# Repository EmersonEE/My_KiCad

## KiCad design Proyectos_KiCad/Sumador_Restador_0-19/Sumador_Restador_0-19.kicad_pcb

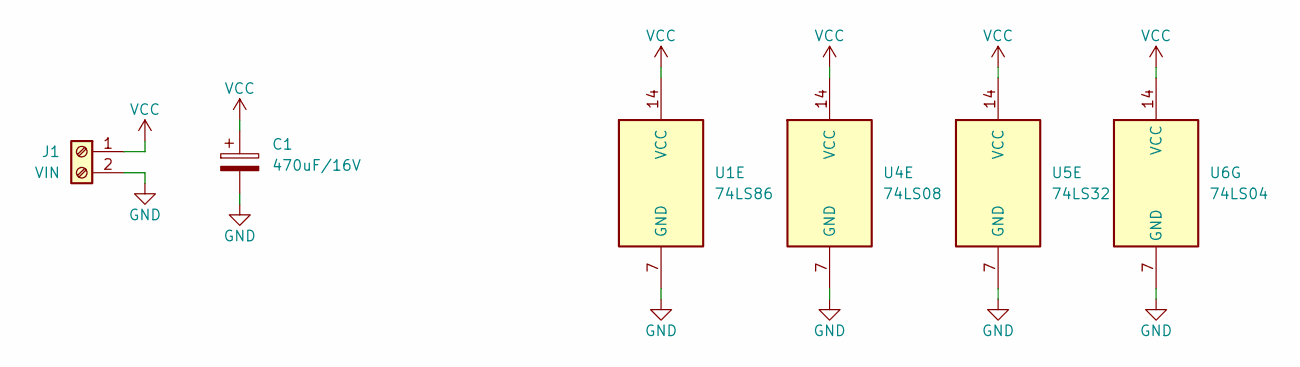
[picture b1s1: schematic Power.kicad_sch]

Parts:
C1: 470uF/16V; CP_Radial_D7.5mm_P2.50mm
J1: VIN; TerminalBlock_Phoenix_MKDS-1,5-2-5.08_1x02_P5.08mm_Horizont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
U1: 74LS86; DIP-14_W7.62mm_LongPads
U4: 74LS08; DIP-14_W7.62mm_LongPads
U5: 74LS32; DIP-14_W7.62mm_LongPads
U6: 74LS04; DIP-14_W7.62mm_LongPads

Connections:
GND: C1.2, J1.2, U1.7 (GND), U4.7 (GND), U5.7 (GND), U6.7 (GND); also elsewhere on the board
VCC: C1.1, J1.1, U1.14 (VCC), U4.14 (VCC), U5.14 (VCC), U6.14 (VCC); also elsewhere on the board

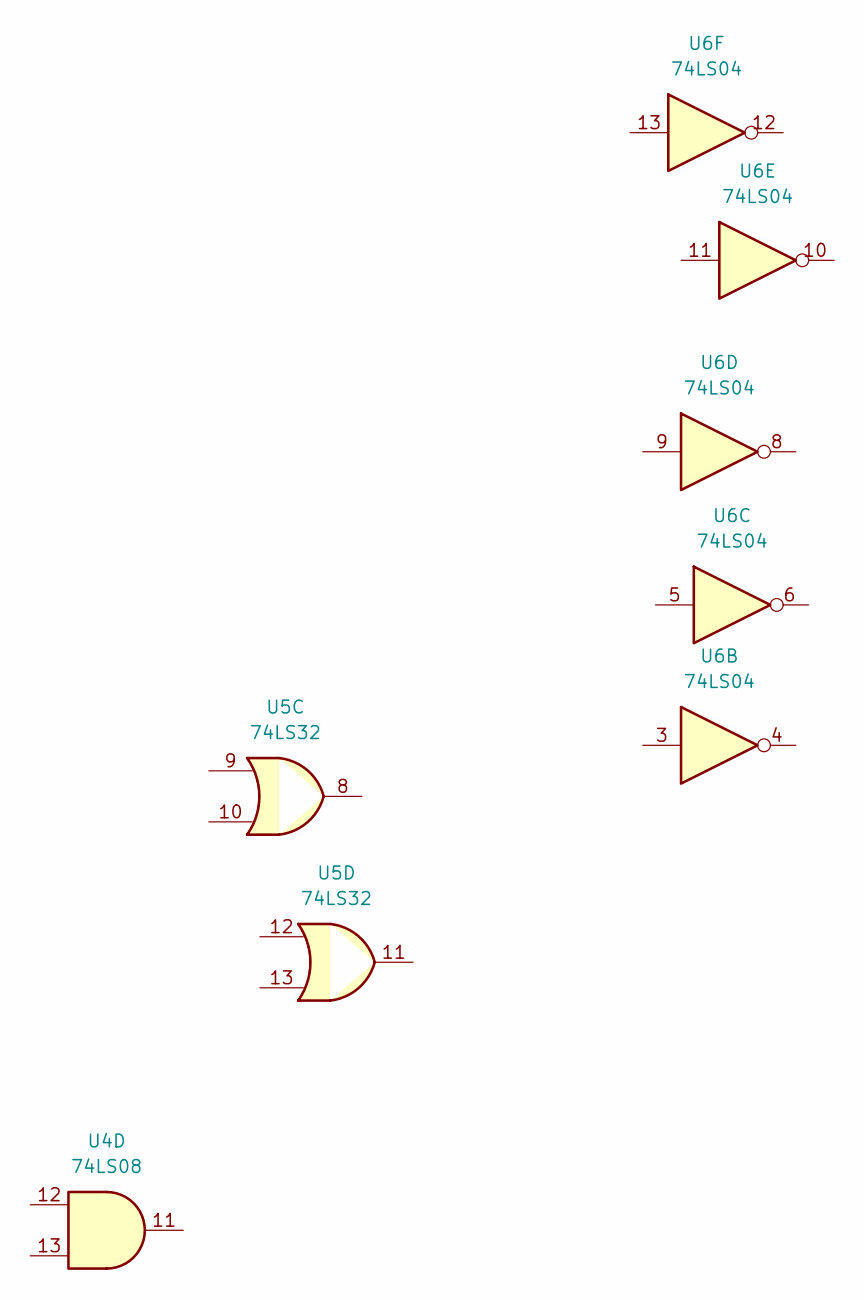
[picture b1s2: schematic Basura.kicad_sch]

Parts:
U4: 74LS08; DIP-14_W7.62mm_LongPads
U5: 74LS32; DIP-14_W7.62mm_LongPads
U6: 74LS04; DIP-14_W7.62mm_LongPads

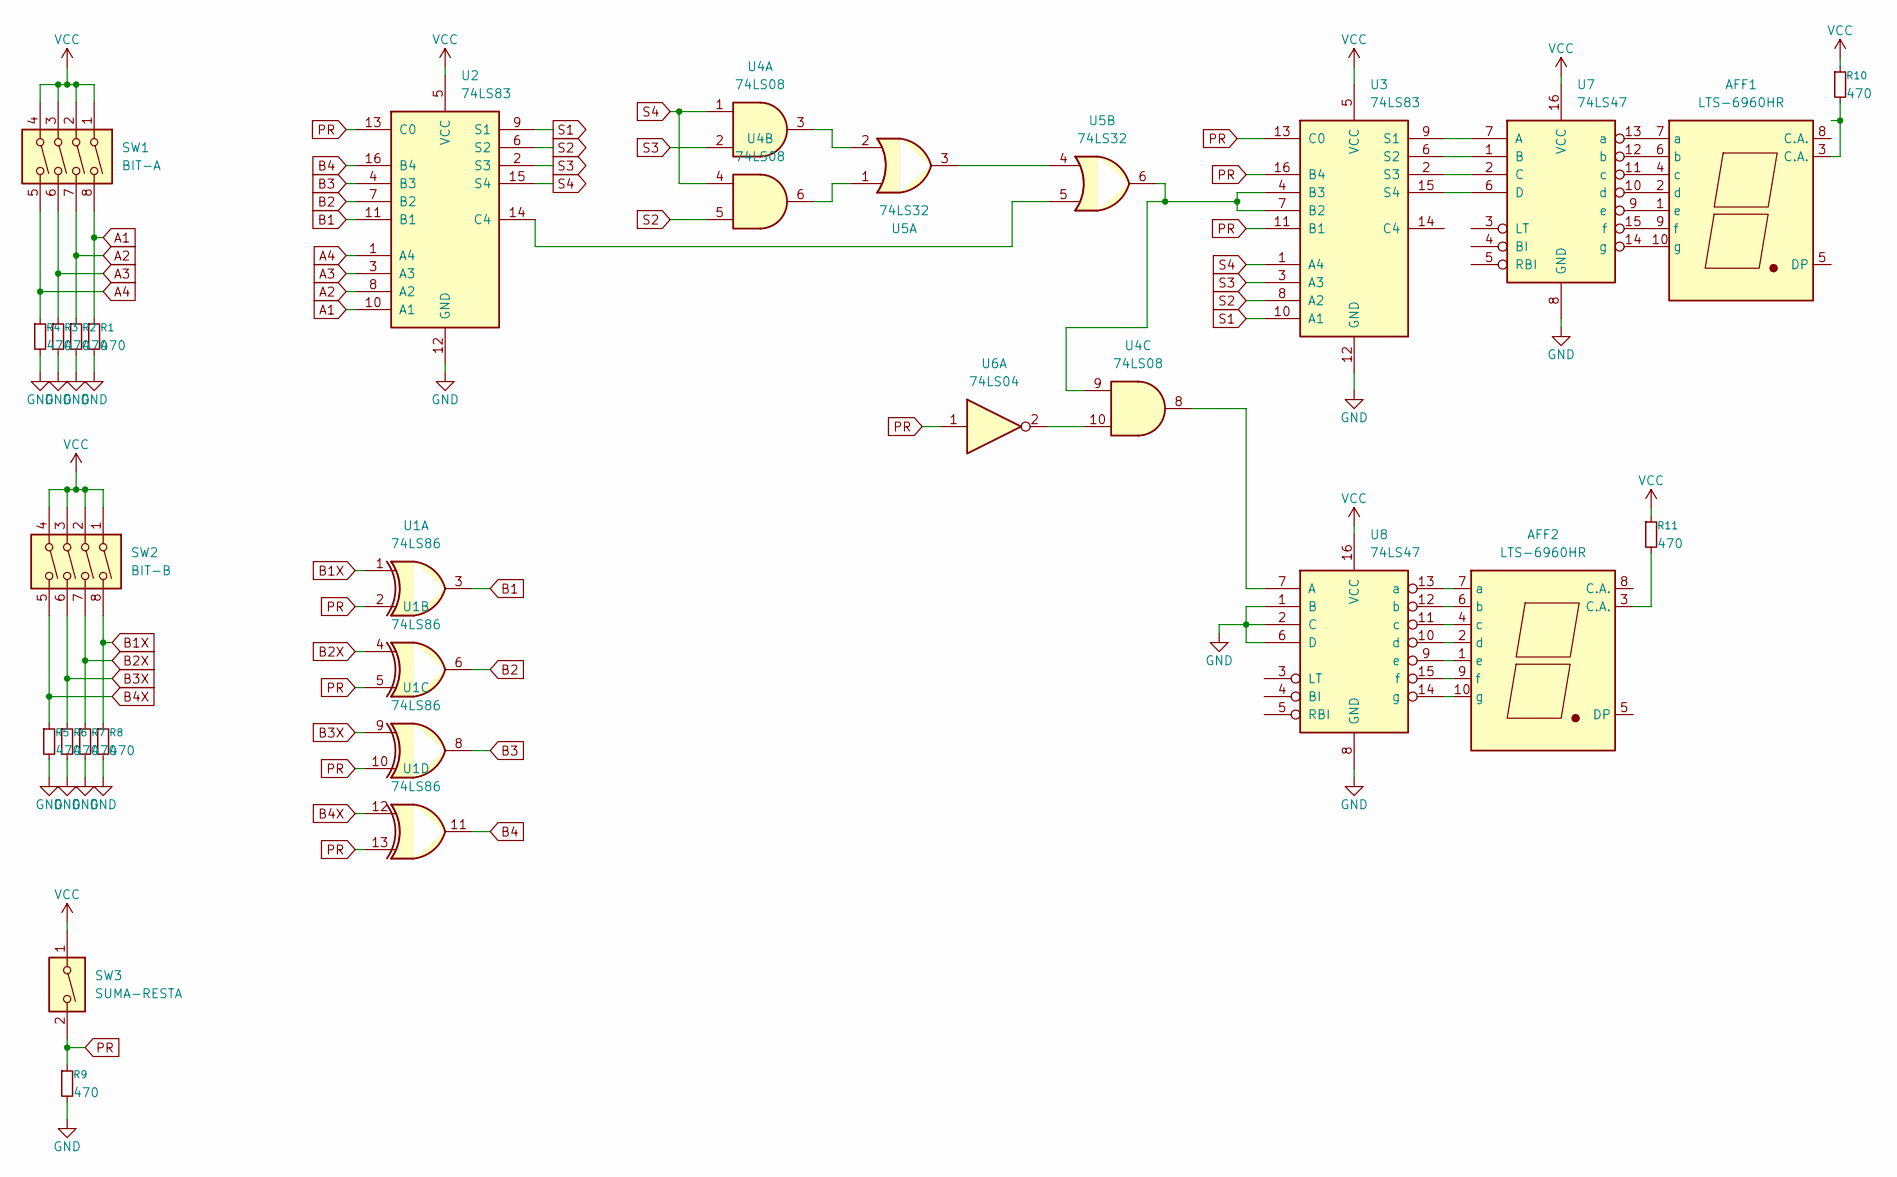
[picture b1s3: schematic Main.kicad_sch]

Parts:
AFF1, AFF2: LTS-6960HR; 7SegmentLED_LTS6760_LTS6780
R1, R2, R3, R4, R5, R6, R7, R8, R9, R10, R11: 470
SW1: BIT-A; SW_DIP_SPSTx04_Slide_9.78x12.34mm_W7.62mm_P2.54mm
SW2: BIT-B; SW_DIP_SPSTx04_Slide_9.78x12.34mm_W7.62mm_P2.54mm
SW3: SUMA-RESTA; SW_DIP_SPSTx01_Slide_9.78x4.72mm_W7.62mm_P2.54mm
U1: 74LS86; DIP-14_W7.62mm_LongPads
U2, U3: 74LS83; DIP-16_W7.62mm_LongPads
U4: 74LS08; DIP-14_W7.62mm_LongPads
U5: 74LS32; DIP-14_W7.62mm_LongPads
U6: 74LS04; DIP-14_W7.62mm_LongPads
U7, U8: 74LS47; DIP-16_W7.62mm_LongPads

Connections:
A1: R1.1, SW1.8, U2.10 (A1)
A2: R2.1, SW1.7, U2.8 (A2)
A3: R3.1, SW1.6, U2.3 (A3)
A4: R4.1, SW1.5, U2.1 (A4)
B1: U1.3, U2.11 (B1)
B1X: R8.1, SW2.8, U1.1
B2: U1.6, U2.7 (B2)
B2X: R7.1, SW2.7, U1.4
B3: U1.8, U2.4 (B3)
B3X: R6.1, SW2.6, U1.9
B4: U1.11, U2.16 (B4)
B4X: R5.1, SW2.5, U1.12
GND: R1.2, R2.2, R3.2, R4.2, R5.2, R6.2, R7.2, R8.2, R9.2, U2.12 (GND), U3.12 (GND), U7.8 (GND), U8.1 (B), U8.2 (C), U8.6 (D), U8.8 (GND); also elsewhere on the board
unnamed: AFF1.3 (C.A.), R10.2
unnamed: AFF1.7 (a), U7.13 (a)
unnamed: AFF1.6 (b), U7.12 (b)
unnamed: AFF1.4 (c), U7.11 (c)
unnamed: AFF1.2 (d), U7.10 (d)
unnamed: AFF1.1 (e), U7.9 (e)
unnamed: AFF1.9 (f), U7.15 (f)
unnamed: AFF1.10 (g), U7.14 (g)
unnamed: AFF2.3 (C.A.), R11.2
unnamed: AFF2.7 (a), U8.13 (a)
unnamed: AFF2.6 (b), U8.12 (b)
unnamed: AFF2.4 (c), U8.11 (c)
unnamed: AFF2.2 (d), U8.10 (d)
unnamed: AFF2.1 (e), U8.9 (e)
unnamed: AFF2.9 (f), U8.15 (f)
unnamed: AFF2.10 (g), U8.14 (g)
unnamed: U2.14 (C4), U5.5
unnamed: U3.4 (B3), U3.7 (B2), U4.9, U5.6
unnamed: U3.9 (S1), U7.7 (A)
unnamed: U3.6 (S2), U7.1 (B)
unnamed: U3.2 (S3), U7.2 (C)
unnamed: U3.15 (S4), U7.6 (D)
unnamed: U4.3, U5.2
unnamed: U4.6, U5.1
unnamed: U4.10, U6.2
unnamed: U5.3, U5.4
unnamed: U4.8, U8.7 (A)
PR: R9.1, SW3.2, U1.2, U1.5, U1.10, U1.13, U2.13 (C0), U3.11 (B1), U3.13 (C0), U3.16 (B4), U6.1
S1: U2.9 (S1), U3.10 (A1)
S2: U2.6 (S2), U3.8 (A2), U4.5
S3: U2.2 (S3), U3.3 (A3), U4.2
S4: U2.15 (S4), U3.1 (A4), U4.1, U4.4
VCC: R10.1, R11.1, SW1.1, SW1.2, SW1.3, SW1.4, SW2.1, SW2.2, SW2.3, SW2.4, SW3.1, U2.5 (VCC), U3.5 (VCC), U7.16 (VCC), U8.16 (VCC); also elsewhere on the board

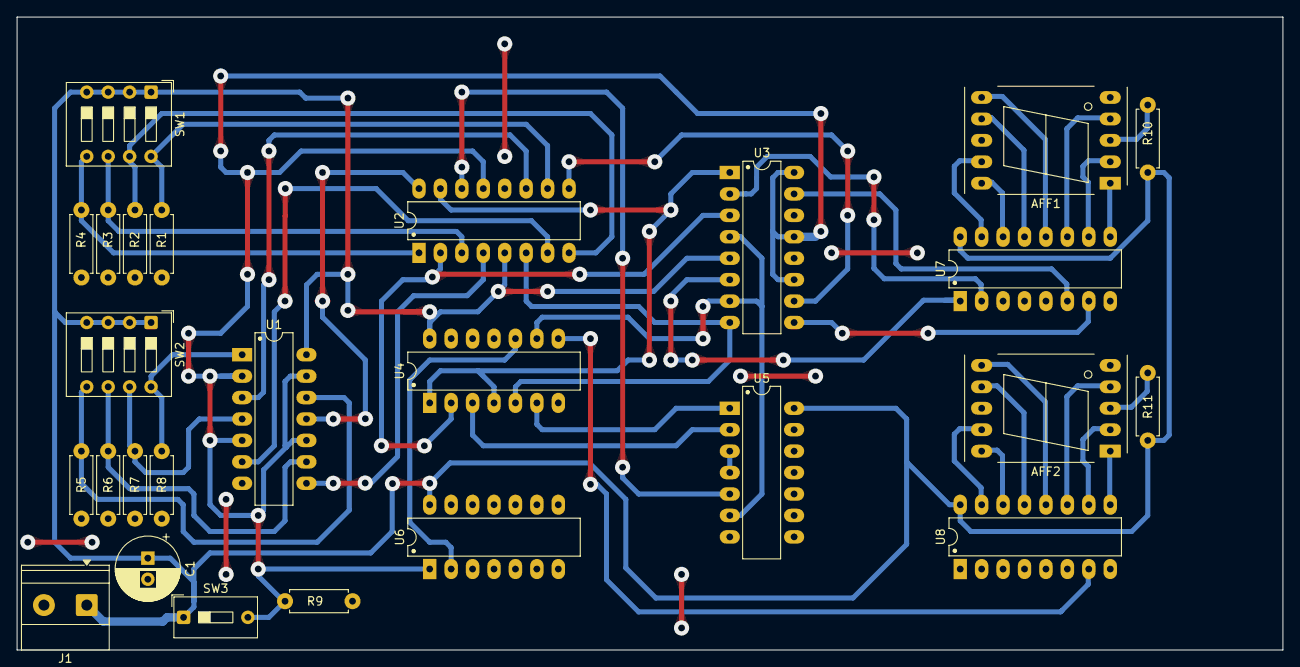
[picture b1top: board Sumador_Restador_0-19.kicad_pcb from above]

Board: 2 copper layers, 150.0 x 75.0 mm, 26 parts (0 on the bottom side), 46 nets.

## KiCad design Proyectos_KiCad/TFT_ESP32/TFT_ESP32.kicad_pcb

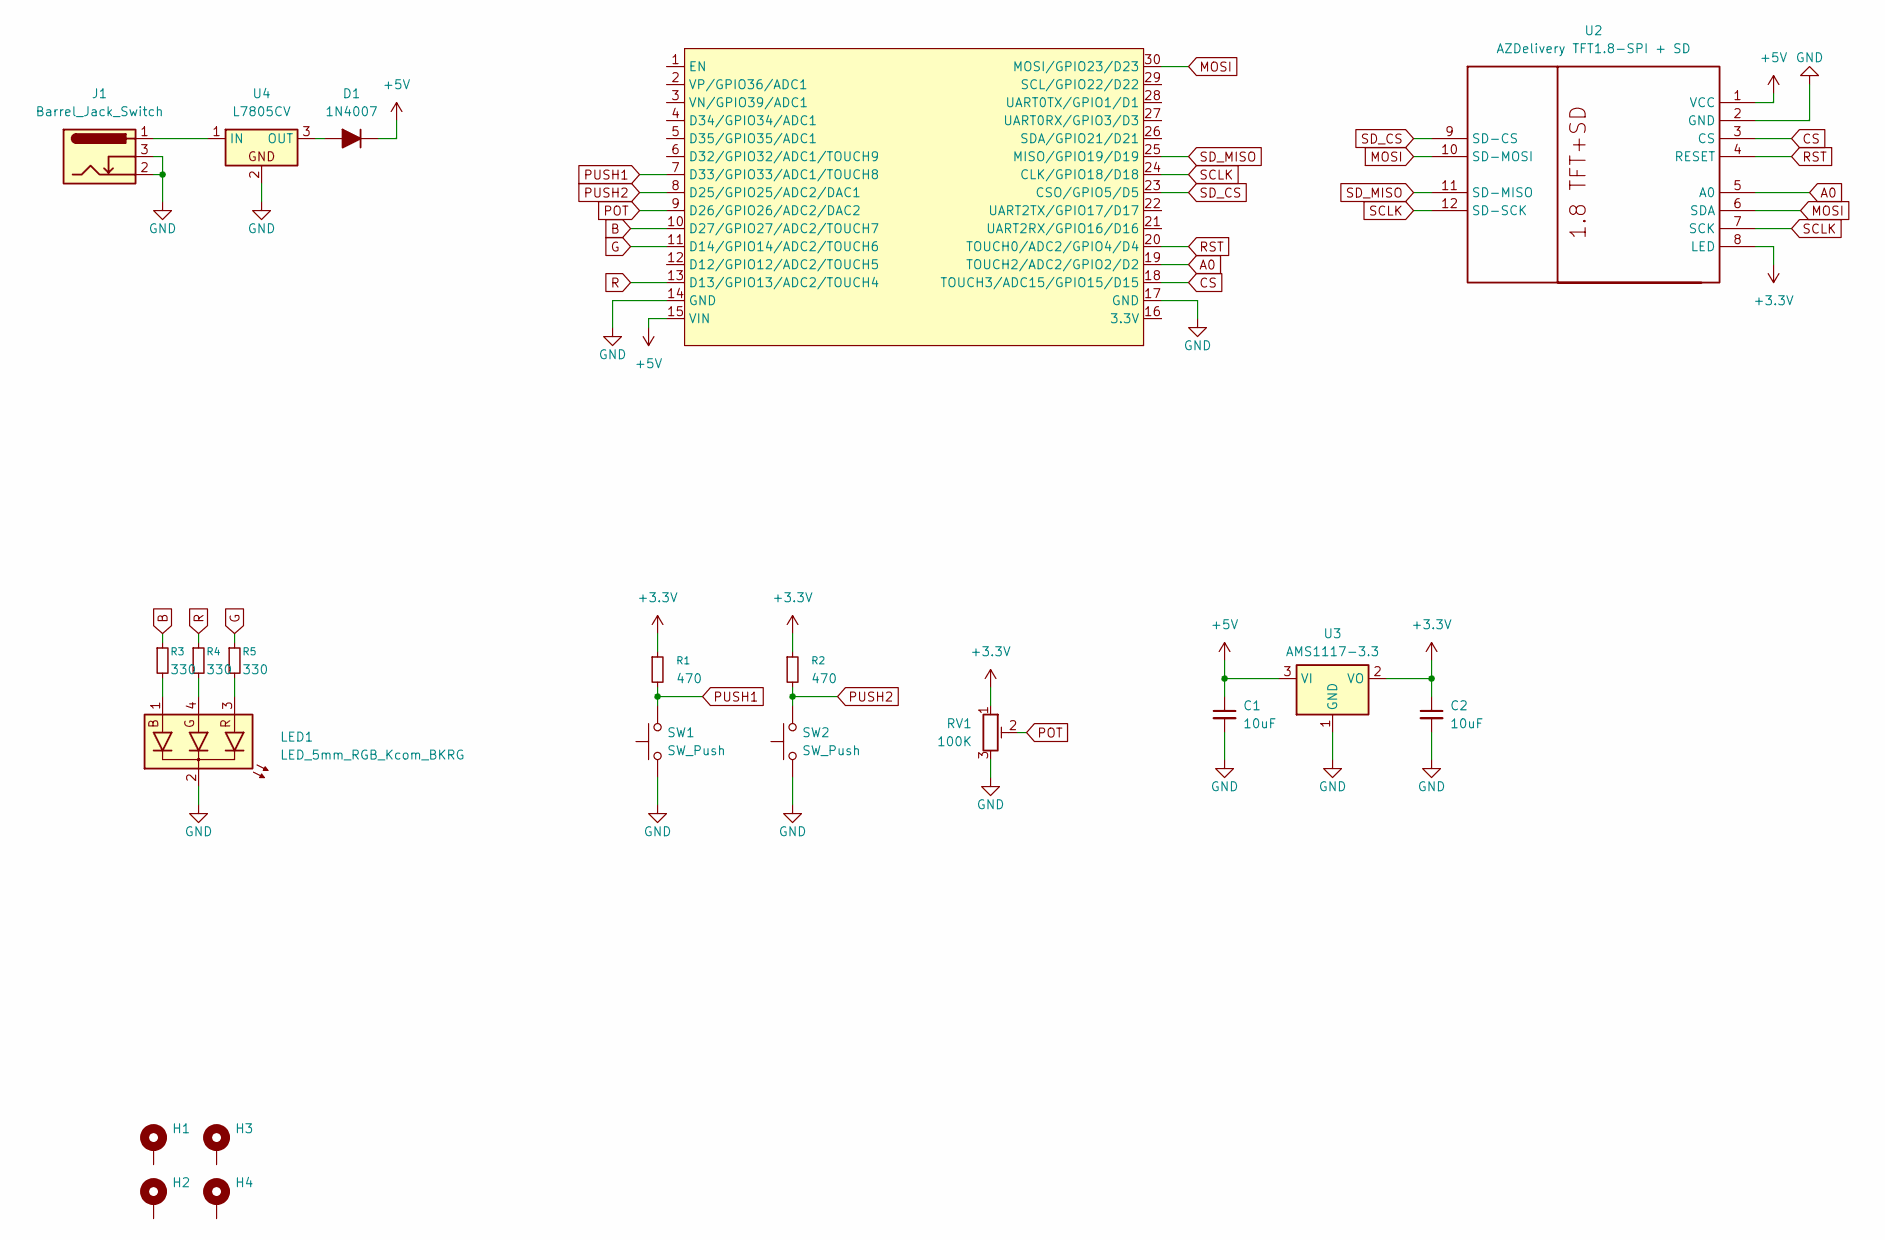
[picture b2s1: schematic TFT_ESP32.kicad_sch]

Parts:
C1, C2: 10uF; C_0805_2012Metric_Pad1.18x1.45mm_HandSolder
D1: 1N4007; D_DO-41_SOD81_P7.62mm_Horizontal
H1, H2, H3, H4: MountingHole_Pad; MountingHole_3.2mm_M3_Pad_Via
J1: Barrel_Jack_Switch; BarrelJack_GCT_DCJ200-10-A_Horizontal
LED1: LED_5mm_RGB_Kcom_BKRG; LED_D5.0mm-4_RGB_Wide_Pins
R1, R2: 470; R_0805_2012Metric_Pad1.20x1.40mm_HandSolder
R3, R4, R5: 330; R_0805_2012Metric_Pad1.20x1.40mm_HandSolder
RV1: 100K; Potentiometer_Bourns_3266Y_Vertical
SW1, SW2: SW_Push; SW_PUSH_6mm
U1: ESP32_DevKit_V1_DOIT; ESP32_DEVKIT_V1_E32
U2: AZDelivery TFT1.8-SPI + SD; 1.8TFT+SD; Manufacturer Part ST7735
U3: AMS1117-3.3; SOT-223-3_TabPin2
U4: L7805CV; TO-220-3_Vertical

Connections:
+3.3V: C2.1, R1.1, R2.1, RV1.1, U2.8 (LED), U3.2 (VO)
+5V: C1.1, D1.1 (K), U1.15 (VIN), U2.1 (VCC), U3.3 (VI)
A0: U1.19 (TOUCH2/ADC2/GPIO2/D2), U2.5 (A0)
B: R3.1, U1.10 (D27/GPIO27/ADC2/TOUCH7)
CS: U1.18 (TOUCH3/ADC15/GPIO15/D15), U2.3 (CS)
G: R5.1, U1.11 (D14/GPIO14/ADC2/TOUCH6)
GND: C1.2, C2.2, J1.2, J1.3, LED1.2 (A), RV1.3, SW1.1, SW2.1, U1.14 (GND), U1.17 (GND), U2.2 (GND), U3.1 (GND), U4.2
MOSI: U1.30 (MOSI/GPIO23/D23), U2.6 (SDA), U2.10 (SD-MOSI)
unnamed: D1.2 (A), U4.3 (OUT)
unnamed: LED1.1 (B), R3.2
unnamed: LED1.4 (G), R4.2
unnamed: LED1.3 (R), R5.2
unnamed: J1.1, U4.1 (IN)
POT: RV1.2, U1.9 (D26/GPIO26/ADC2/DAC2)
PUSH1: R1.2, SW1.2, U1.7 (D33/GPIO33/ADC1/TOUCH8)
PUSH2: R2.2, SW2.2, U1.8 (D25/GPIO25/ADC2/DAC1)
R: R4.1, U1.13 (D13/GPIO13/ADC2/TOUCH4)
RST: U1.20 (TOUCH0/ADC2/GPIO4/D4), U2.4 (RESET)
SCLK: U1.24 (CLK/GPIO18/D18), U2.7 (SCK), U2.12 (SD-SCK)
SD_CS: U1.23 (CSO/GPIO5/D5), U2.9 (SD-CS)
SD_MISO: U1.25 (MISO/GPIO19/D19), U2.11 (SD-MISO)

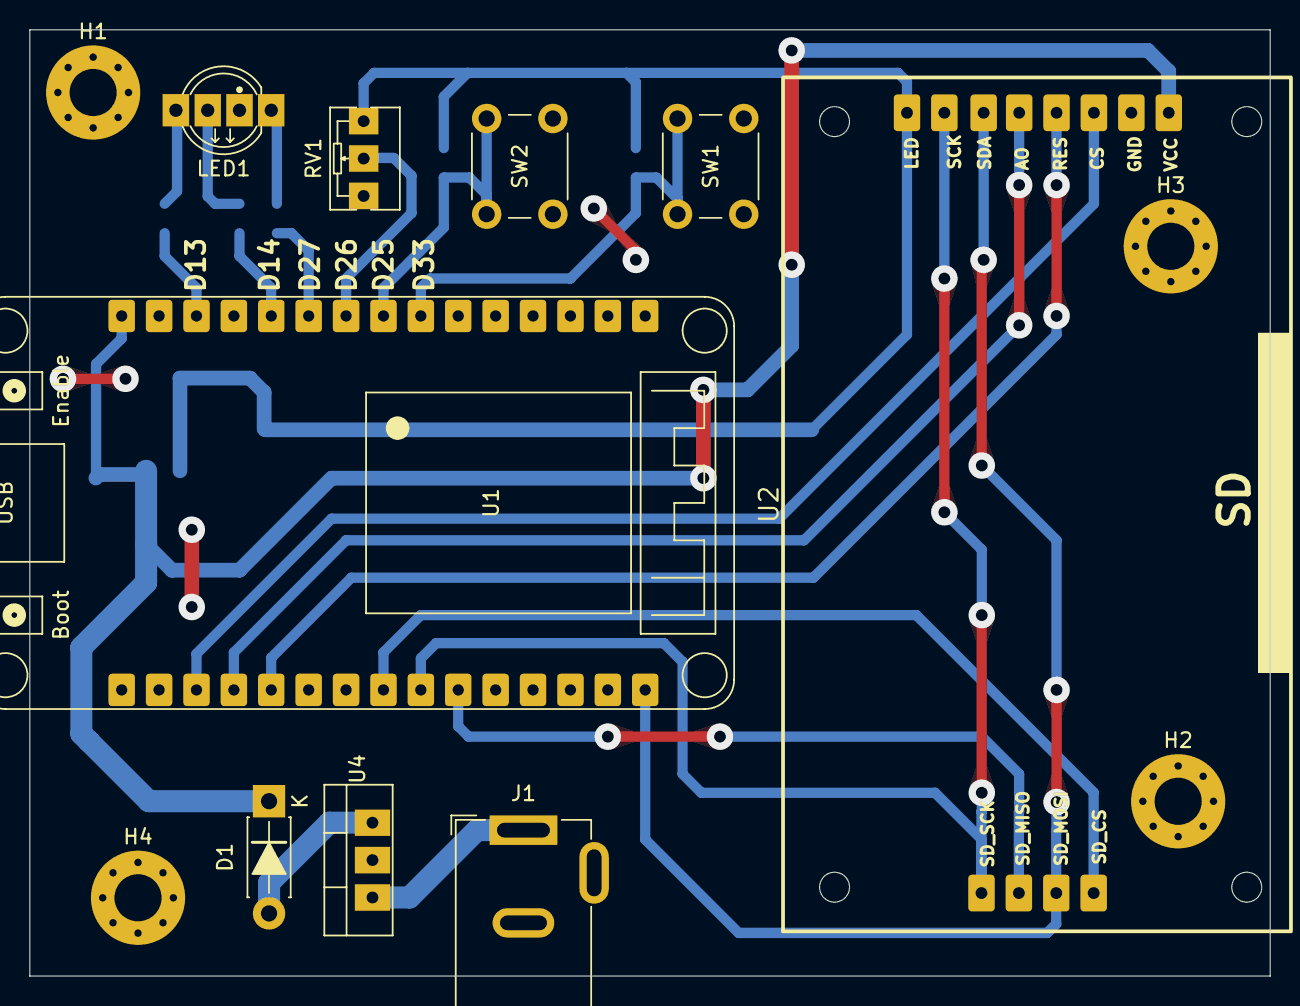
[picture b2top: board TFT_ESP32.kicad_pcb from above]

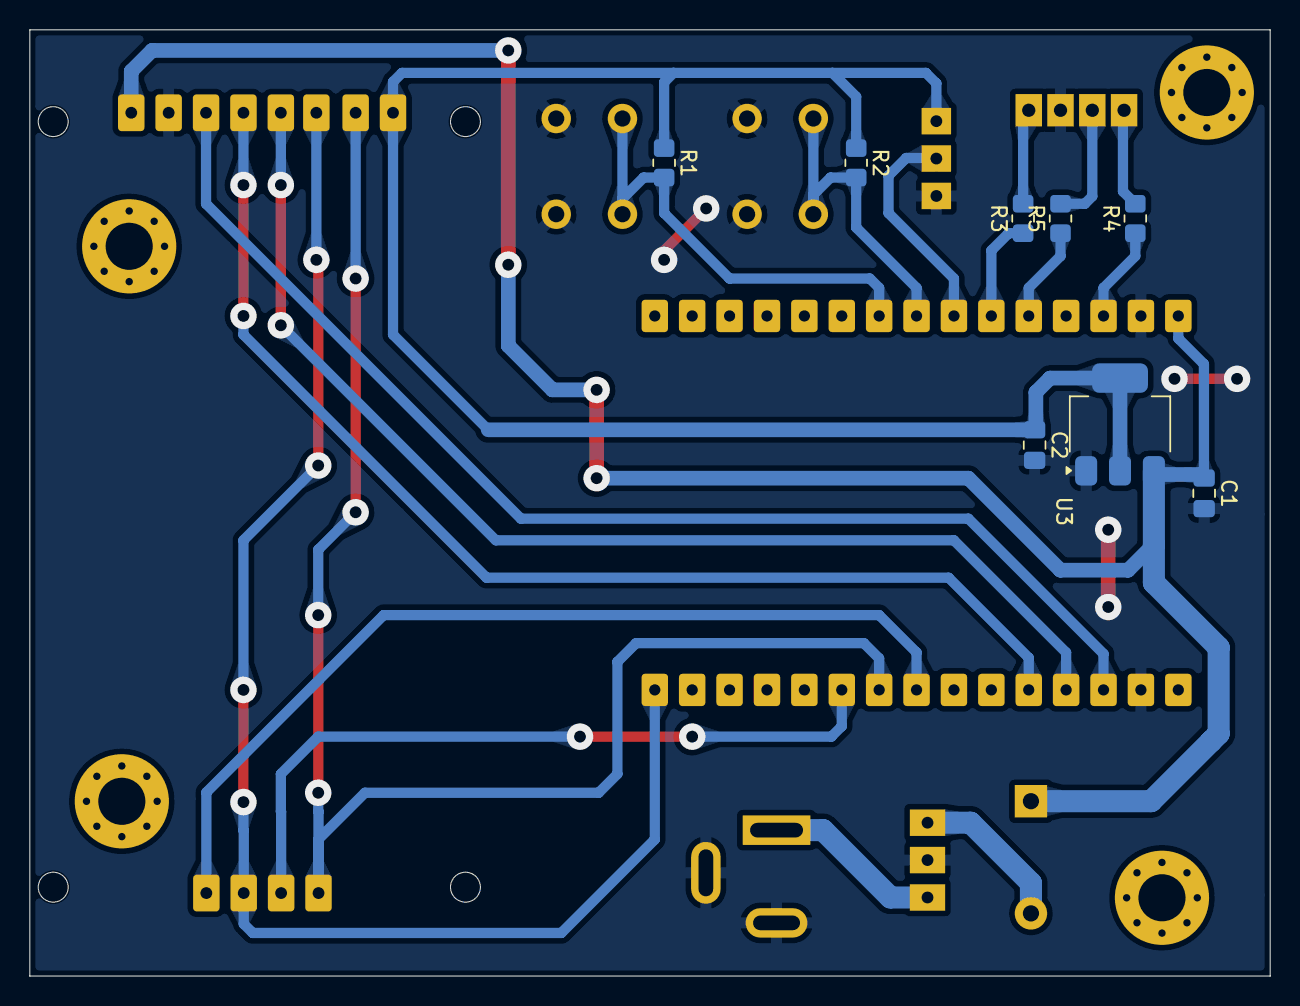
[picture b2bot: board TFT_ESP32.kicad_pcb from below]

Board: 2 copper layers, 84.2 x 64.3 mm, 21 parts (8 on the bottom side), 21 nets.

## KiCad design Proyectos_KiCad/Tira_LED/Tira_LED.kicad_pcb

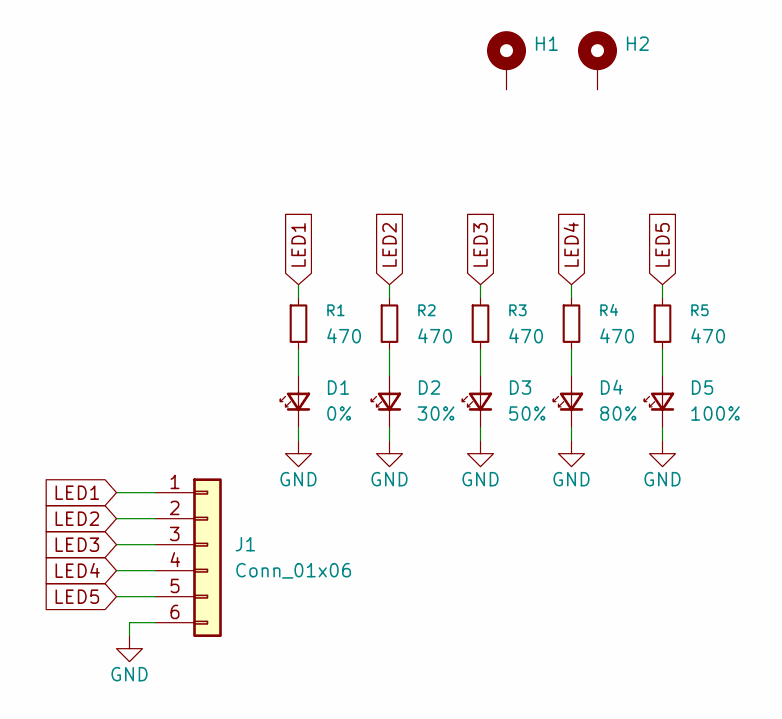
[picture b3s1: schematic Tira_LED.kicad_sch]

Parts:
D1: 0%; LED_1210_3225Metric_Pad1.42x2.65mm
D2: 30%; LED_1210_3225Metric_Pad1.42x2.65mm
D3: 50%; LED_1210_3225Metric_Pad1.42x2.65mm
D4: 80%; LED_1210_3225Metric_Pad1.42x2.65mm
D5: 100%; LED_1210_3225Metric_Pad1.42x2.65mm
H1, H2: MountingHole_3.2mm_M3_Pad_Via
J1: Conn_01x06; PinHeader_1x06_P2.54mm_Vertical
R1, R2, R3, R4, R5: 470; R_0805_2012Metric_Pad1.20x1.40mm_HandSolder

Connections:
GND: D1.1 (K), D2.1 (K), D3.1 (K), D4.1 (K), D5.1 (K), J1.6
LED1: J1.1, R1.1
LED2: J1.2, R2.1
LED3: J1.3, R3.1
LED4: J1.4, R4.1
LED5: J1.5, R5.1
unnamed: D1.2 (A), R1.2
unnamed: D2.2 (A), R2.2
unnamed: D3.2 (A), R3.2
unnamed: D4.2 (A), R4.2
unnamed: D5.2 (A), R5.2

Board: 2 copper layers, 13 parts (1 on the bottom side), 11 nets, no tracks yet.

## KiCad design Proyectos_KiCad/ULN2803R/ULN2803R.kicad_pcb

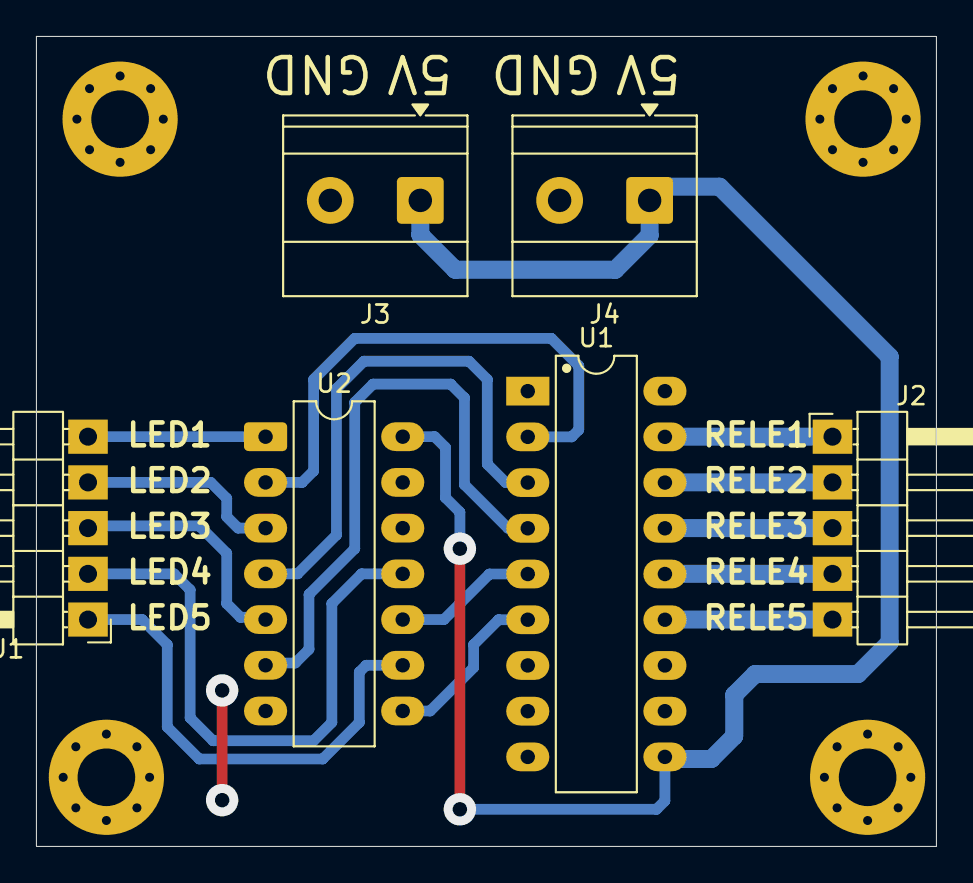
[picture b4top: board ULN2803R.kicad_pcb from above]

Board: 2 copper layers, 50.0 x 45.0 mm, 10 parts (0 on the bottom side), 17 nets.

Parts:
H1, H2, H3, H4: MountingHole_3.2mm_M3_Pad_Via
J1: IN; PinHeader_1x05_P2.54mm_Horizontal
J2: OUT; PinHeader_1x05_P2.54mm_Horizontal
J3: CARGADOR; TerminalBlock_Phoenix_MKDS-1,5-2_1x02_P5.00mm_Horizontal
J4: RELES; TerminalBlock_Phoenix_MKDS-1,5-2_1x02_P5.00mm_Horizontal
U1: ULN2803A; DIP-18_W7.62mm_LongPads
U2: 74LS14; CERDIP-14_W7.62mm_SideBrazed_LongPads

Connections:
GND: J3.2, J4.2, U1.9 (GND), U2.7 (GND)
unnamed: J1.1, U2.9
unnamed: J1.2, U2.11
unnamed: J1.3, U2.5
unnamed: J1.4, U2.3
unnamed: J1.5, U2.1
unnamed: J2.1, U1.17 (O2)
unnamed: J2.2, U1.16 (O3)
unnamed: J2.3, U1.15 (O4)
unnamed: J2.4, U1.14 (O5)
unnamed: J2.5, U1.13 (O6)
unnamed: U1.2 (I2), U2.2
unnamed: U1.3 (I3), U2.4
unnamed: U1.4 (I4), U2.6
unnamed: U1.5 (I5), U2.10
unnamed: U1.6 (I6), U2.8
VCC: J3.1, J4.1, U1.10 (COM), U2.14 (VCC)

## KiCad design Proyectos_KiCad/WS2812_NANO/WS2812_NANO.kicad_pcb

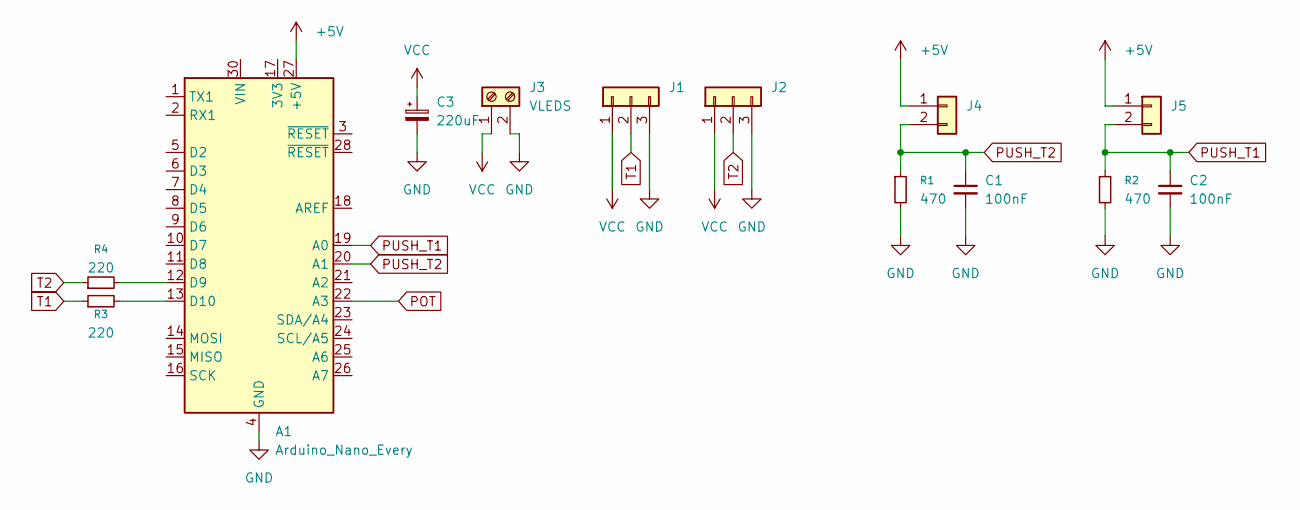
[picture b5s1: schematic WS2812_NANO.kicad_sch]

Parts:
A1: Arduino_Nano_Every; Arduino_Nano
C1, C2: 100nF; C_Disc_D3.8mm_W2.6mm_P2.50mm
C3: 220uF; CP_Radial_D5.0mm_P2.00mm
J1, J2: Conn_01x03; PinHeader_1x03_P2.54mm_Vertical
J3: VLEDS; TerminalBlock_Phoenix_MKDS-1,5-2-5.08_1x02_P5.08mm_Horizont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
J4, J5: Conn_01x02; PinHeader_1x02_P2.54mm_Vertical
R1, R2: 470; R_1210_3225Metric_Pad1.30x2.65mm_HandSolder
R3, R4: 220; 1K

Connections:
+5V: A1.27 (+5V), J4.1, J5.1
GND: A1.4 (GND), A1.29 (GND), C1.2, C2.2, C3.2, J1.3, J2.3, J3.2, R1.2, R2.2
unnamed: A1.12 (D9), R4.2
unnamed: A1.13 (D10), R3.2
POT: A1.22 (A3)
PUSH_T1: A1.19 (A0), C2.1, J5.2, R2.1
PUSH_T2: A1.20 (A1), C1.1, J4.2, R1.1
T1: J1.2, R3.1
T2: J2.2, R4.1
VCC: C3.1, J1.1, J2.1, J3.1

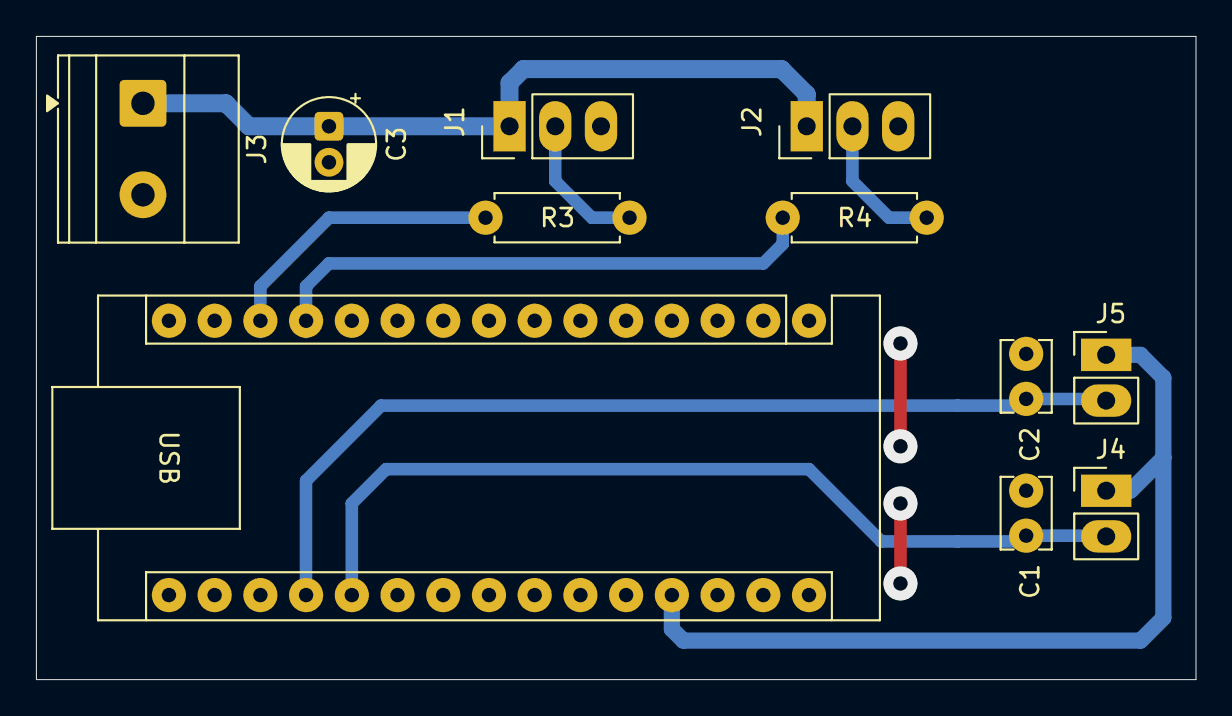
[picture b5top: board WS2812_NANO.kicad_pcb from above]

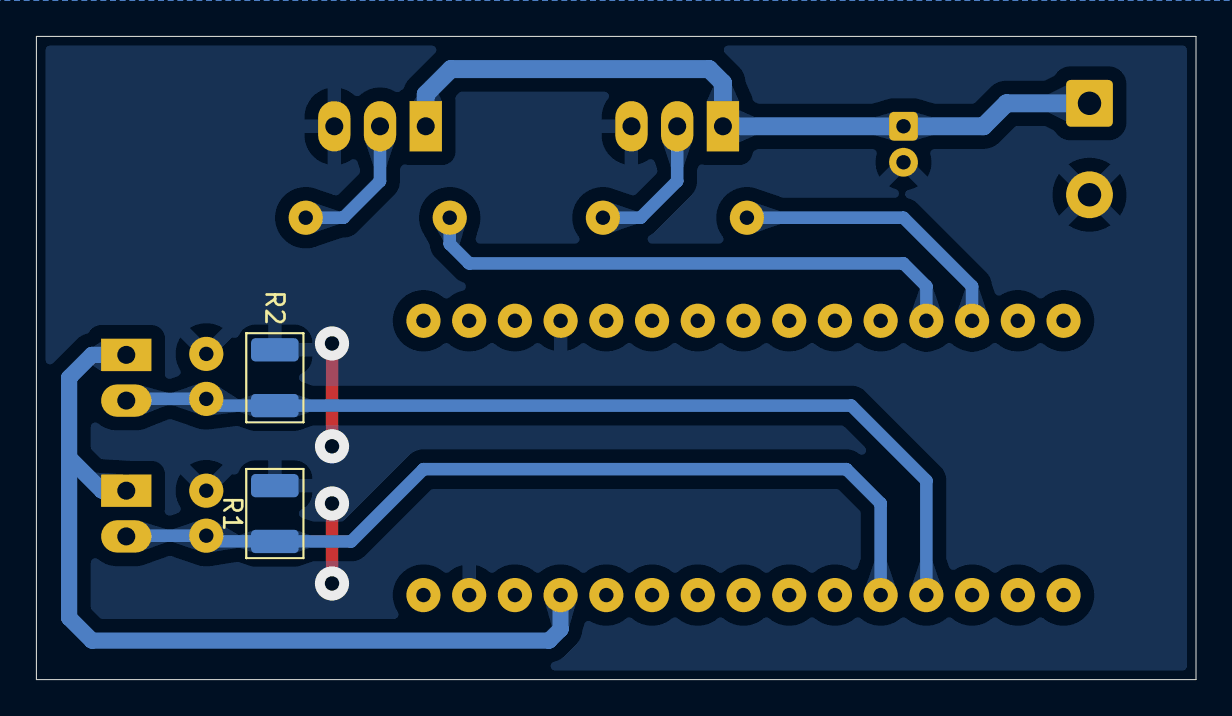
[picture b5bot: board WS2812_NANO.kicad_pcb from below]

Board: 2 copper layers, 64.4 x 35.7 mm, 13 parts (2 on the bottom side), 9 nets.

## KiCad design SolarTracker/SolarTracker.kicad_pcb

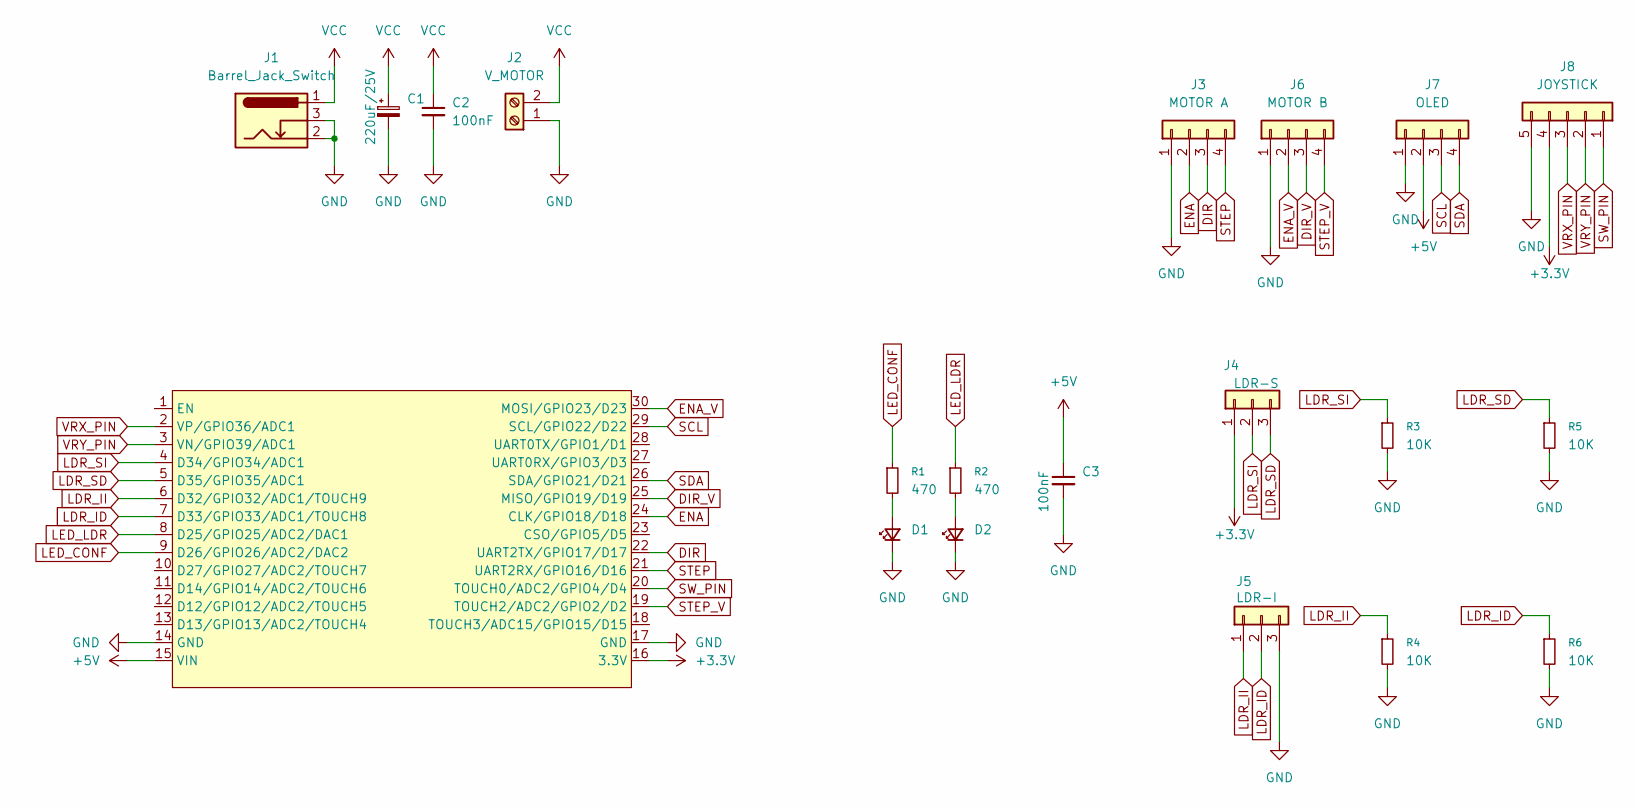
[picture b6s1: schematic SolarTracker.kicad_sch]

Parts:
C1: 220uF/25V; CP_Radial_D6.3mm_P2.50mm
C2, C3: 100nF; C_Disc_D3.8mm_W2.6mm_P2.50mm
D1, D2: LED_D5.0mm
J1: Barrel_Jack_Switch; BarrelJack_Horizontal
J2: V_MOTOR; TerminalBlock_Phoenix_MKDS-1,5-2-5.08_1x02_P5.08mm_Horizont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
J3: MOTOR A; Molex_KK-254_AE-6410-04A_1x04_P2.54mm_Vertical
J4: LDR-S; Molex_KK-254_AE-6410-03A_1x03_P2.54mm_Vertical
J5: LDR-I; Molex_KK-254_AE-6410-03A_1x03_P2.54mm_Vertical
J6: MOTOR B; Molex_KK-254_AE-6410-04A_1x04_P2.54mm_Vertical
J7: OLED; PinSocket_1x04_P2.54mm_Vertical
J8: JOYSTICK; PinSocket_1x05_P2.54mm_Vertical
R1, R2: 470; R_Axial_DIN0207_L6.3mm_D2.5mm_P10.16mm_Horizontal
R3, R4, R5, R6: 10K; R_Axial_DIN0207_L6.3mm_D2.5mm_P10.16mm_Horizontal
U1: ESP32_DevKit_V1_DOIT; ESP32_DEVKIT_V1_E32

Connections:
+3.3V: J4.1, J8.4, U1.16 (3.3V)
+5V: C3.1, J7.2, U1.15 (VIN)
DIR: J3.3, U1.22 (UART2TX/GPIO17/D17)
DIR_V: J6.3, U1.25 (MISO/GPIO19/D19)
ENA: J3.2, U1.24 (CLK/GPIO18/D18)
ENA_V: J6.2, U1.30 (MOSI/GPIO23/D23)
GND: C1.2, C2.2, C3.2, D1.1 (K), D2.1 (K), J1.2, J1.3, J2.1, J3.1, J5.3, J6.1, J7.1, J8.5, R3.2, R4.2, R5.2, R6.2, U1.14 (GND), U1.17 (GND)
LDR_ID: J5.2, R6.1, U1.7 (D33/GPIO33/ADC1/TOUCH8)
LDR_II: J5.1, R4.1, U1.6 (D32/GPIO32/ADC1/TOUCH9)
LDR_SD: J4.3, R5.1, U1.5 (D35/GPIO35/ADC1)
LDR_SI: J4.2, R3.1, U1.4 (D34/GPIO34/ADC1)
LED_CONF: R1.1, U1.9 (D26/GPIO26/ADC2/DAC2)
LED_LDR: R2.1, U1.8 (D25/GPIO25/ADC2/DAC1)
unnamed: D1.2 (A), R1.2
unnamed: D2.2 (A), R2.2
SCL: J7.3, U1.29 (SCL/GPIO22/D22)
SDA: J7.4, U1.26 (SDA/GPIO21/D21)
STEP: J3.4, U1.21 (UART2RX/GPIO16/D16)
STEP_V: J6.4, U1.19 (TOUCH2/ADC2/GPIO2/D2)
SW_PIN: J8.1, U1.20 (TOUCH0/ADC2/GPIO4/D4)
VCC: C1.1, C2.1, J1.1, J2.2
VRX_PIN: J8.3, U1.2 (VP/GPIO36/ADC1)
VRY_PIN: J8.2, U1.3 (VN/GPIO39/ADC1)

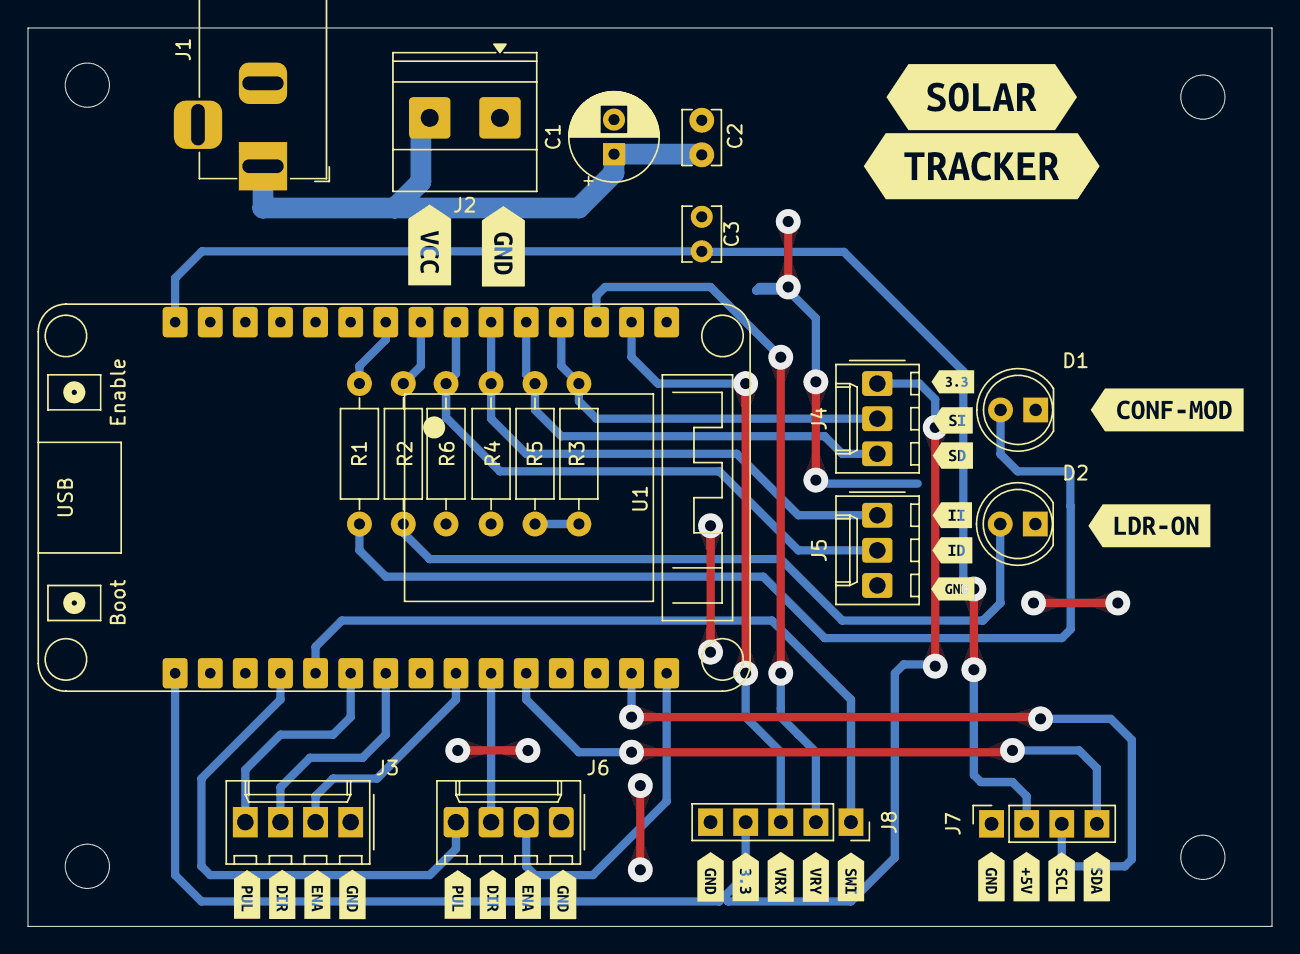
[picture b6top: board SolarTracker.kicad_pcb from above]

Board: 2 copper layers, 90.0 x 65.0 mm, 49 parts (0 on the bottom side), 23 nets.

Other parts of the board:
kibuzzard-67F1E4A8: G***; kibuzzard-67F1E4A8
kibuzzard-67F1E4B2: G***; kibuzzard-67F1E4B2
kibuzzard-67F1E4DB: G***; kibuzzard-67F1E4DB
kibuzzard-67F1E4E2: G***; kibuzzard-67F1E4E2
kibuzzard-67F1E4EA: G***; kibuzzard-67F1E4EA
kibuzzard-67F1E5DB, kibuzzard-67F1E5DB#2: G***; kibuzzard-67F1E5DB
kibuzzard-67F1E5E3, kibuzzard-67F1E5E3#2: G***; kibuzzard-67F1E5E3
kibuzzard-67F1E5F0, kibuzzard-67F1E5F0#2, kibuzzard-67F1E5F0#3: G***; kibuzzard-67F1E5F0
kibuzzard-67F1E6A7: G***; kibuzzard-67F1E6A7
kibuzzard-67F1E6AC: G***; kibuzzard-67F1E6AC
kibuzzard-67F1E47E: G***; kibuzzard-67F1E47E
kibuzzard-67F1E62A: G***; kibuzzard-67F1E62A
kibuzzard-67F1E66D: G***; kibuzzard-67F1E66D
kibuzzard-67F1E67F: G***; kibuzzard-67F1E67F
kibuzzard-67F1E69E: G***; kibuzzard-67F1E69E
kibuzzard-67F1E623: G***; kibuzzard-67F1E623
kibuzzard-67F1E673: G***; kibuzzard-67F1E673
kibuzzard-67F1E679: G***; kibuzzard-67F1E679
kibuzzard-67F1E689: G***; kibuzzard-67F1E689
kibuzzard-67F1ECFC: G***; kibuzzard-67F1ECFC
kibuzzard-67F1ED00: G***; kibuzzard-67F1ED00
kibuzzard-67F1ED0E: G***; kibuzzard-67F1ED0E
kibuzzard-67F1ED13: G***; kibuzzard-67F1ED13
kibuzzard-67F2E706: G***; kibuzzard-67F2E706
kibuzzard-67F2E713: G***; kibuzzard-67F2E713
